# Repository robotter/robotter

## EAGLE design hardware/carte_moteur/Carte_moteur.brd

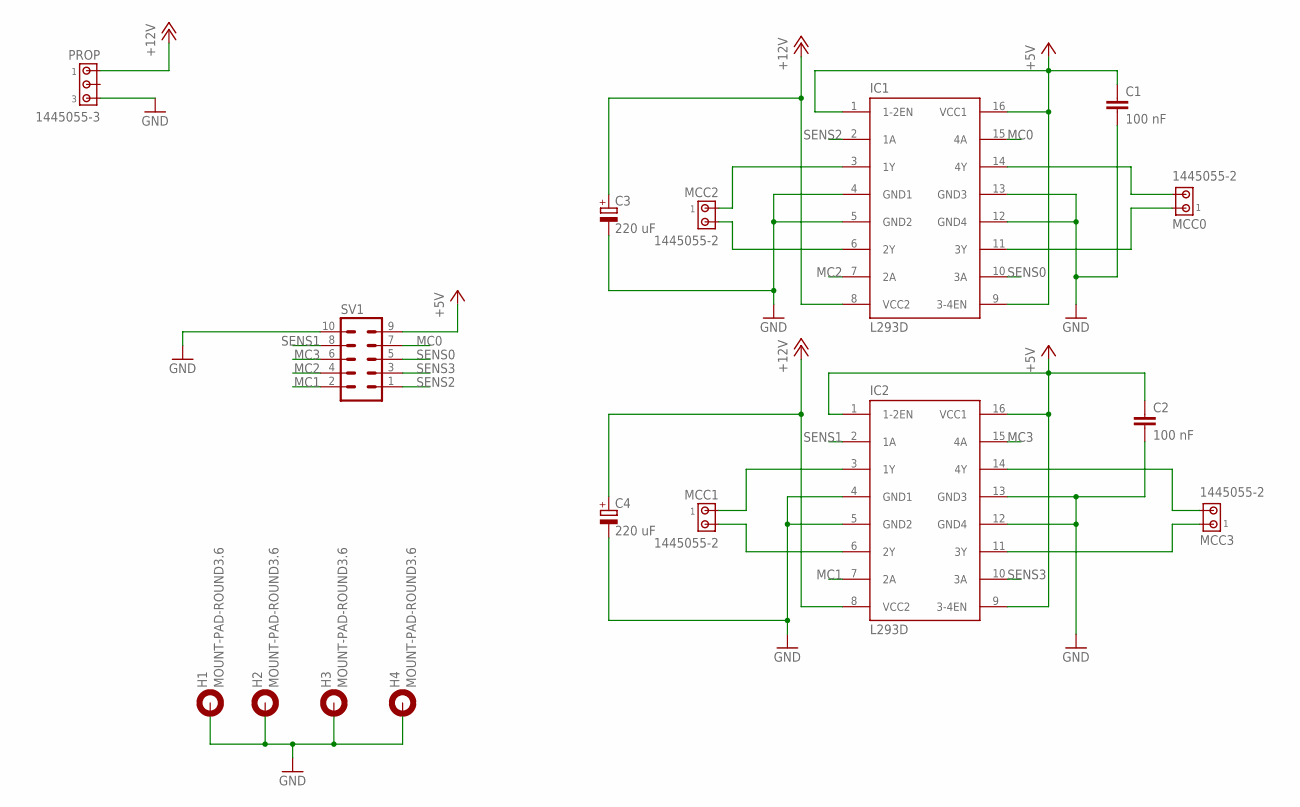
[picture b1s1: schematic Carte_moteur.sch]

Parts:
C1, C2: 100 nF; C0805
C3, C4: 220 uF; PANASONIC_G
H1, H2, H3, H4: MOUNT-PAD-ROUND3.6; 3,6-PAD
IC1, IC2: L293D; DIL16
MCC0, MCC1, MCC2, MCC3: 1445055-2
PROP: 1445055-3
SV1: ML10

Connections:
+5V: C1.1, C2.1, IC1.1 (1-2EN), IC1.9 (3-4EN), IC1.16 (VCC1), IC2.1 (1-2EN), IC2.9 (3-4EN), IC2.16 (VCC1), SV1.9
+12V: C3.+, C4.+, IC1.8 (VCC2), IC2.8 (VCC2), PROP.1
GND: C1.2, C2.2, C3.-, C4.-, H1.B3,6, H2.B3,6, H3.B3,6, H4.B3,6, IC1.4 (GND1), IC1.5 (GND2), IC1.12 (GND4), IC1.13 (GND3), IC2.4 (GND1), IC2.5 (GND2), IC2.12 (GND4), IC2.13 (GND3), PROP.3, SV1.10
MC0: IC1.15 (4A), SV1.7
MC1: IC2.7 (2A), SV1.2
MC2: IC1.7 (2A), SV1.4
MC3: IC2.15 (4A), SV1.6
unnamed: IC1.3 (1Y), MCC2.1
unnamed: IC1.6 (2Y), MCC2.2
unnamed: IC1.14 (4Y), MCC0.2
unnamed: IC1.11 (3Y), MCC0.1
unnamed: IC2.3 (1Y), MCC1.1
unnamed: IC2.6 (2Y), MCC1.2
unnamed: IC2.11 (3Y), MCC3.1
unnamed: IC2.14 (4Y), MCC3.2
SENS0: IC1.10 (3A), SV1.5
SENS1: IC2.2 (1A), SV1.8
SENS2: IC1.2 (1A), SV1.1
SENS3: IC2.10 (3A), SV1.3

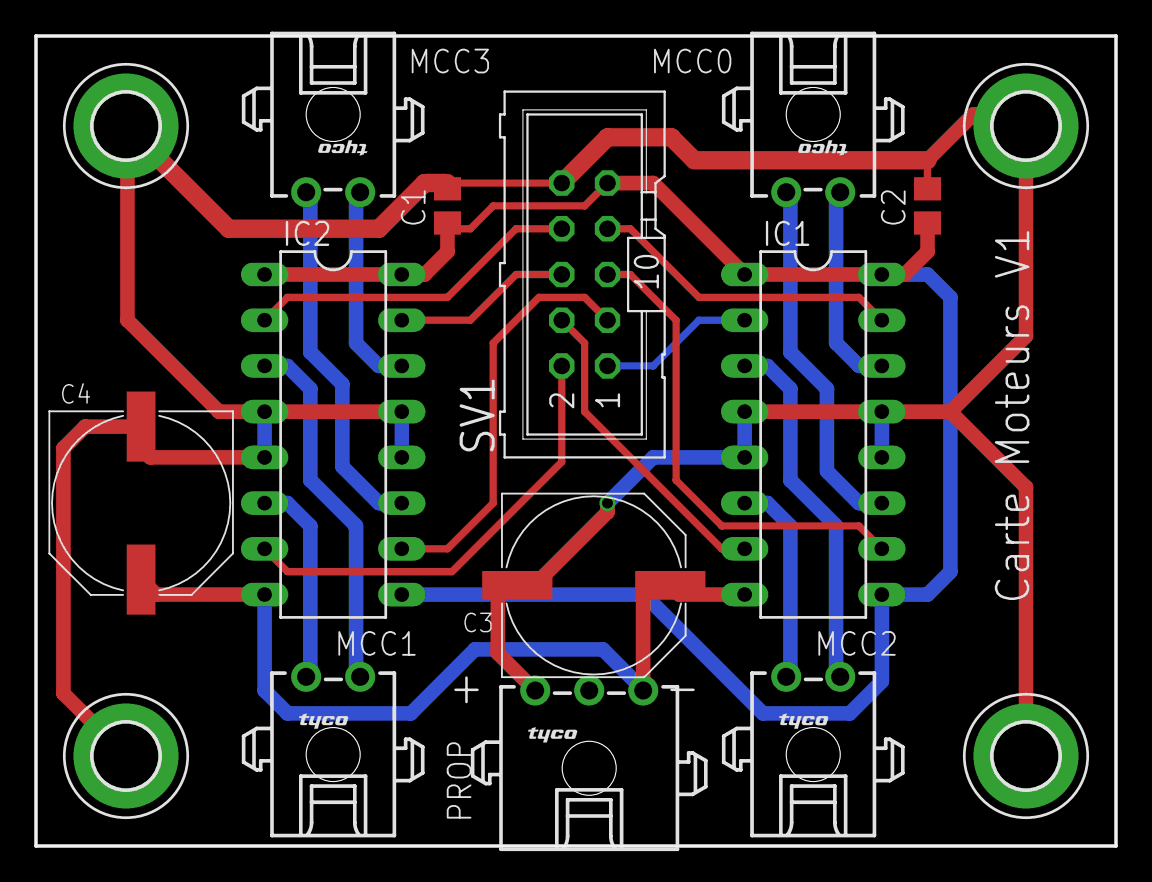
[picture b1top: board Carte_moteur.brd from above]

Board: 2 copper layers, 60.0 x 45.0 mm, 16 parts (0 on the bottom side), 19 nets.
